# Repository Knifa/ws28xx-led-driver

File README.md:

# ws28xx-led-driver

This is a straightforward DIY WS28xx LED driver. It's got these features:

- STM32F103C8T6 used as the microcontroller.
- Intended to be powered by a single-cell Li-ion battery, with USB charging and
  cell protection.
- 5V 1.5Aish step-up for LED power.
- Single button for soft-power and settings.
- 0805 SMD components or thereabouts.

## License

- Firmware under [MIT License](./firmware/LICENSE.md).
- Hardware under [CC-BY-SA-4.0](./hardware/LICENSE.md).

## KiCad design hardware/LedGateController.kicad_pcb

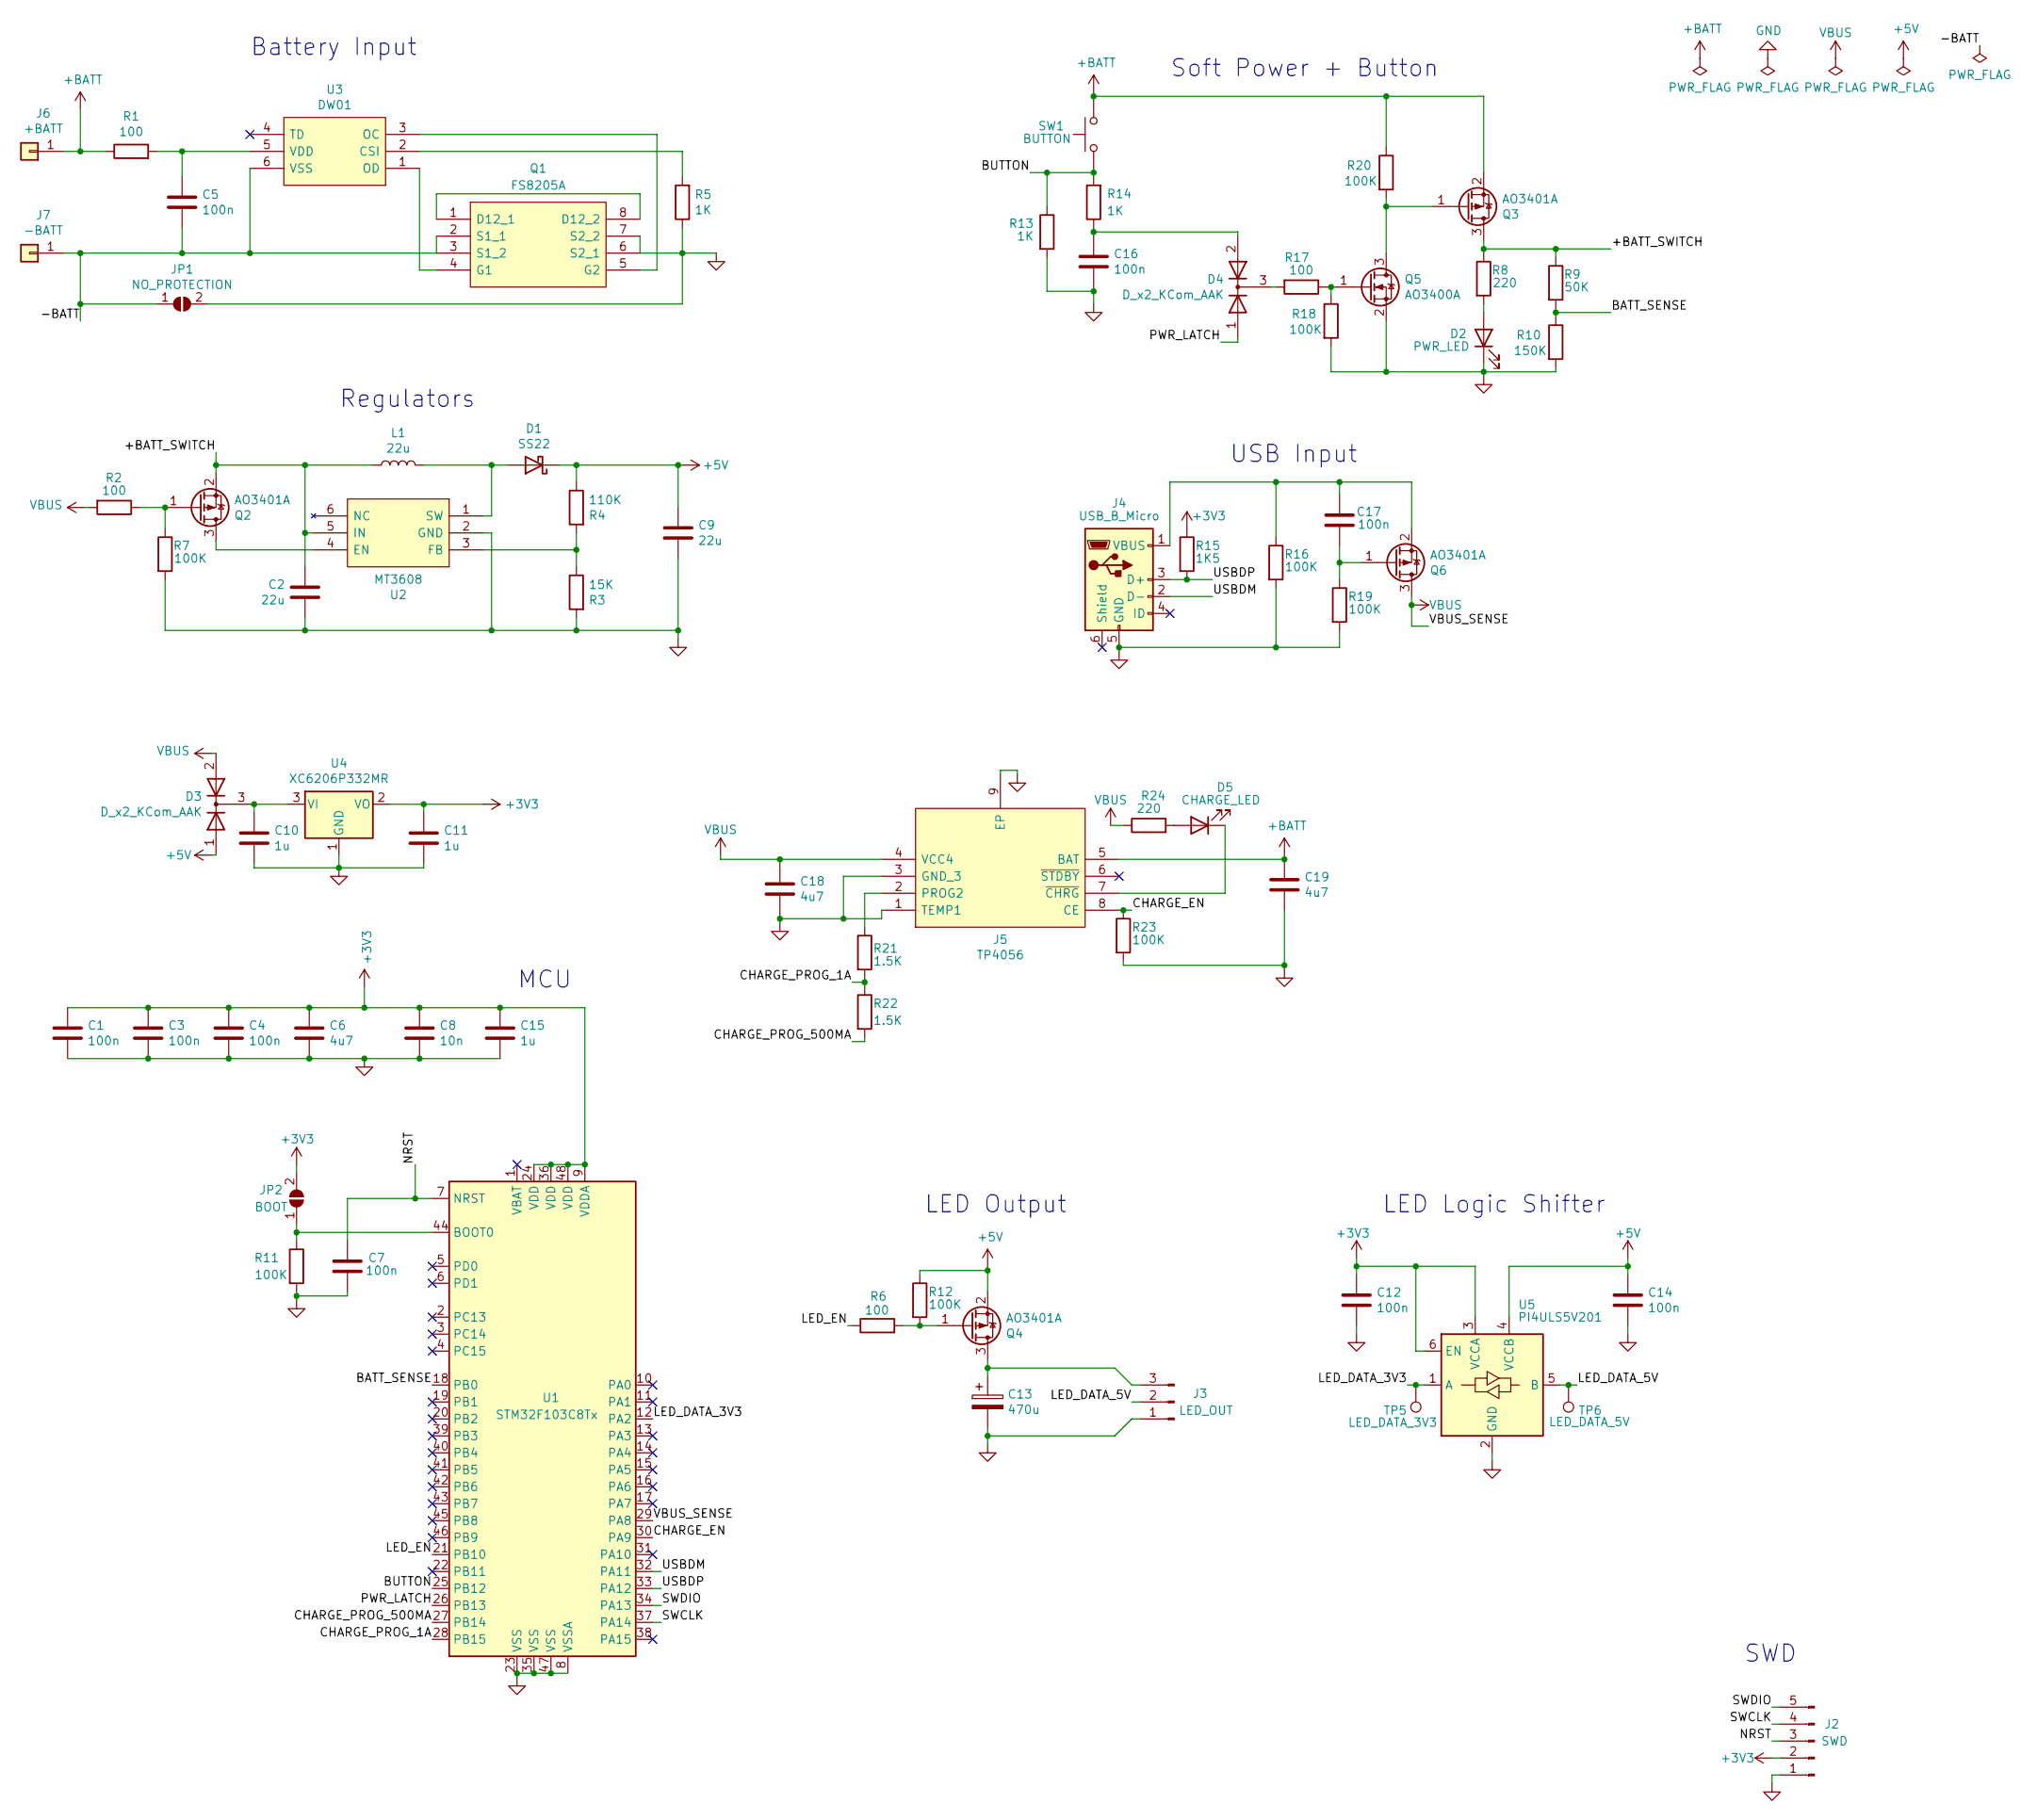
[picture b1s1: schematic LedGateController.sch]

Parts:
C1, C3, C4, C5, C7, C12, C14, C16, C17: 100n; C_0805_2012Metric
C2, C9: 22u; C_0805_2012Metric
C6, C18, C19: 4u7; C_0805_2012Metric
C8: 10n; C_0805_2012Metric
C10, C11, C15: 1u; C_0805_2012Metric
C13: 470u; CP_Elec_10x7.7
D1: SS22; D_SMA_Handsoldering
D2: PWR_LED; LED_0805_2012Metric
D3, D4: D_x2_KCom_AAK; SOT-23
D5: CHARGE_LED; LED_0805_2012Metric
J2: SWD; PinHeader_1x05_P2.54mm_Vertical
J3: LED_OUT; PinHeader_1x03_P2.54mm_Horizontal
J4: USB_B_Micro; U254051T4BHJ25S2S
J5: TP4056; SOIC127P600X175-9N; Manufacturer_Part_Number TP4056
J6: +BATT; Battery Pad
J7: -BATT; Battery Pad
JP1: NO_PROTECTION; SolderJumper-2_P1.3mm_Open_Pad1.0x1.5mm
JP2: BOOT; SolderJumper-2_P1.3mm_Open_Pad1.0x1.5mm
L1: 22u; YT1040-220M
Q1: FS8205A; TSSOP-8_4.4x3mm_P0.65mm; Manufacturer_Part_Number FS8205A
Q2, Q3, Q4, Q6: AO3401A; SOT-23
Q5: AO3400A; SOT-23
R1, R2, R6, R17: 100; R_0805_2012Metric
R3: 15K; R_0805_2012Metric
R4: 110K; R_0805_2012Metric
R5, R13, R14: 1K; R_0805_2012Metric
R7, R11, R12, R16, R18, R19, R20, R23: 100K; R_0805_2012Metric
R8, R24: 220; R_0805_2012Metric
R9: 50K; R_0805_2012Metric
R10: 150K; R_0805_2012Metric
R15: 1K5; R_0805_2012Metric
R21, R22: 1.5K; R_0805_2012Metric
SW1: BUTTON; TS-1009B-04326
TP5: LED_DATA_3V3; TestPoint_Pad_D1.0mm
TP6: LED_DATA_5V; TestPoint_Pad_D1.0mm
U1: STM32F103C8Tx; LQFP-48_7x7mm_P0.5mm
U2: MT3608; SOT-23-6; Manufacturer_Part_Number MT3608
U3: DW01; SOT-23-6; Manufacturer_Part_Number DW01
U4: XC6206P332MR; SOT-23
U5: PI4ULS5V201; SOT-23-6

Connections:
+3V3: C1.1, C3.1, C4.1, C6.1, C8.1, C11.1, C12.1, C15.1, J2.2, JP2.2 (B), R15.1, U1.9 (VDDA), U1.24 (VDD), U1.36 (VDD), U1.48 (VDD), U4.2 (VO), U5.3 (VCCA), U5.6 (EN)
+5V: C9.1, C14.1, D1.1 (K), D3.1 (A), Q4.2 (S), R4.1, R12.1, U5.4 (VCCB)
+BATT: C19.1, J5.5 (BAT), J6.1, Q3.2 (S), R1.1, R20.1, SW1.2; also elsewhere on the board
/+BATT_SWITCH: C2.1, L1.1, Q2.2 (S), Q3.3 (D), R8.1, R9.1, U2.5 (IN)
/-BATT: C5.2, J7.1, JP1.1 (A), Q1.2 (S1_1), Q1.3 (S1_2), U3.6 (VSS)
/BATT_SENSE: R9.2, R10.1, U1.18 (PB0)
/BUTTON: R13.1, R14.2, SW1.1, U1.25 (PB12)
/CHARGE_EN: J5.8 (CE), R23.1, U1.30 (PA9)
/CHARGE_PROG_1A: R21.2, R22.1, U1.28 (PB15)
/CHARGE_PROG_500MA: R22.2, U1.27 (PB14)
/LED_DATA_3V3: TP5.1, U1.12 (PA2), U5.1 (A)
/LED_DATA_5V: J3.2, TP6.1, U5.5 (B)
/LED_EN: R6.1, U1.21 (PB10)
/NRST: C7.2, J2.3, U1.7 (NRST)
/PWR_LATCH: D4.1 (A), U1.26 (PB13)
/SWCLK: J2.4, U1.37 (PA14)
/SWDIO: J2.5, U1.34 (PA13)
/USBDM: J4.2 (D-), U1.32 (PA11)
/USBDP: J4.3 (D+), R15.2, U1.33 (PA12)
GND: C1.2, C2.2, C3.2, C4.2, C6.2, C7.1, C8.2, C9.2, C10.2, C11.2, C12.2, C13.2, C14.2, C15.2, C16.2, C18.2, C19.2, D2.1 (K), J2.1, J3.1, J4.5 (GND), J5.1 (TEMP1), J5.3 (GND_3), J5.9 (EP), JP1.2 (B), Q1.6 (S2_1), Q1.7 (S2_2), Q5.2 (S), R3.2, R5.1, R7.2, R10.2, R11.2, R13.2, R16.2, R18.2, R19.2, R23.2, U1.8 (VSSA), U1.23 (VSS), U1.35 (VSS), U1.47 (VSS), U2.2 (GND), U4.1 (GND), U5.2 (GND)
unnamed: C5.1, R1.2, U3.5 (VDD)
unnamed: C10.1, D3.3 (K), U4.3 (VI)
unnamed: C13.1, J3.3, Q4.3 (D)
unnamed: C16.1, D4.2 (A), R14.1
unnamed: C17.1, J4.1 (VBUS), Q6.2 (S), R16.1
unnamed: C17.2, Q6.1 (G), R19.1
unnamed: D1.2 (A), L1.2, U2.1 (SW)
unnamed: D2.2 (A), R8.2
unnamed: D4.3 (K), R17.2
unnamed: D5.1 (K), J5.7 (~CHRG)
unnamed: D5.2 (A), R24.2
unnamed: J5.2 (PROG2), R21.1
unnamed: JP2.1 (A), R11.1, U1.44 (BOOT0)
unnamed: Q1.1 (D12_1), Q1.8 (D12_2)
unnamed: Q1.4 (G1), U3.1 (OD)
unnamed: Q1.5 (G2), U3.3 (OC)
unnamed: Q2.1 (G), R2.1, R7.1
unnamed: Q2.3 (D), U2.4 (EN)
unnamed: Q3.1 (G), Q5.3 (D), R20.2
unnamed: Q4.1 (G), R6.2, R12.2
unnamed: Q5.1 (G), R17.1, R18.1
unnamed: R3.1, R4.2, U2.3 (FB)
unnamed: R5.2, U3.2 (CSI)
VBUS: C18.1, D3.2 (A), J5.4 (VCC4), Q6.3 (D), R2.2, R24.1, U1.29 (PA8)

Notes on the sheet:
Regulators
MCU
SWD
Battery Input
LED Output
LED Logic Shifter
Soft Power + Button
USB Input

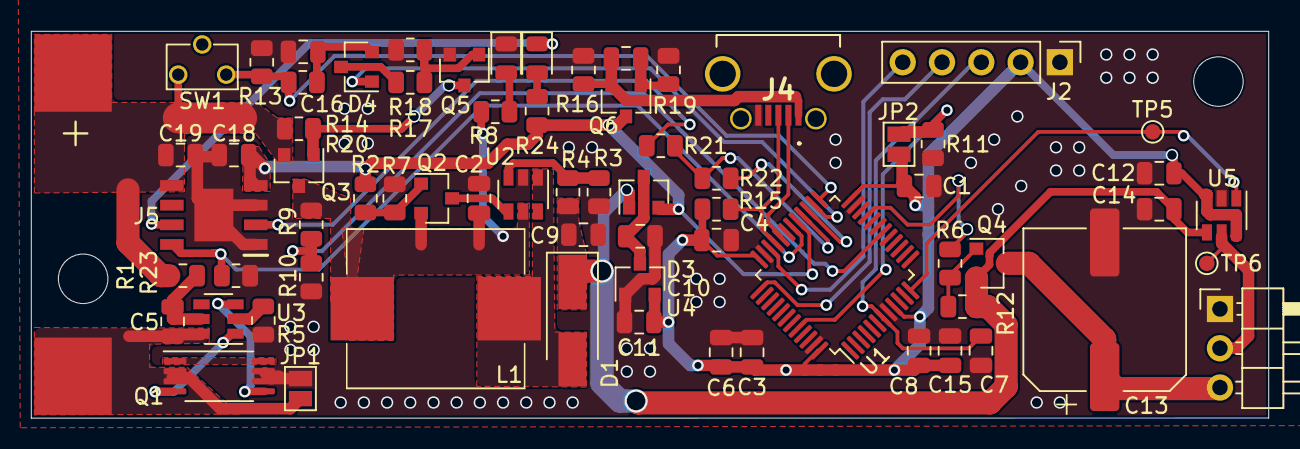
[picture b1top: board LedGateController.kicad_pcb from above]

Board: 2 copper layers, 80.0 x 25.0 mm, 71 parts (0 on the bottom side), 44 nets.

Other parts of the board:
+: +BATT; Battery Pad

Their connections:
+BATT: +.1; also elsewhere on the board

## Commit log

2020-03-30 Move to footprints
2020-04-24 nearly done
2020-04-28 Rev. 1 nearly ready!
2020-04-28 Fix inductor schematic
2020-07-21 Fix battery orientation
2020-07-21 Bring in SamacSys parts used in project
2020-07-21 Change rev. text
2020-07-21 Tidy up some loose tracks
2020-07-21 Remove unneeded ground vias
2020-09-24 Update inductor footprint
2020-09-24 Add new parts
2020-09-24 Update schematic
2021-01-07 Rewire top section
2021-02-07 Rev 2
2021-02-25 rev 2 ordered
2021-03-30 monorepo it up
2021-03-30 add license
2021-03-30 oopsy woopsie
